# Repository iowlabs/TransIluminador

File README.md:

# TransIluminador

Un transiluminador es un instrumento utilizado en experimentos de biología molecular principalmente en procesos de electroforesis en aplicaciones de PCR, clonación, secuenciación o detección de ADN. Su principio se basa en transmitir luz de longitud e intensidad específica a travez de una muestra, lo cual permite visualizar proteinas específicas o ADN.

Para efectos de la instrumentación, consiste en un dispositivo que controla una gran cantidad de LEDs. De este modo, el dipositivo debe encargarse de generar los voltajes de operación y la corriente de los LEDs. Las variables objetivo para ser controladas son:

- voltaje de operación.
- Intensidad de iluminación.
- Tiempo de exposición.

En algunos dispositivos más complejos existen variables como tipos de curva de iluminación, o algunos cuentan con cámaras para la obtención de imagenes en el dispositivo mismo.
asdavsd

## Requisitos del dispositivo.

El dispositivo a desarrollar debe contar con las siguientes caracteristicas:

1. Alimentación de entrada de 12V. De esto se desprende que el dispositivo debe contar con un regulador DCDC tipo boost para los LEDs.

2. Capacidad de controlar diferentes configuraciónes de LEDs de salida.

3. Control de intensidad de los LEDs por medio de un control lineal de corriente.

4. Driver de corriente de hasta 1A por canal.

4. Capacidad para controlar de forma simultanea 2 canales.

5. Lazo de control para monitoreo y calibración de intensidad luminica.

6. Microcontrolador integrado.

7. Modo de operación manual, stand-alone con curvas pre-configuradas o modo de conexión a un host( pc o web app).

8. Monitoreo de la temperatura de los LEDs y sensor de temperatura externo.

9. Interfaz de usuario por medio de panel y pantalla OLED.

## Revisión del componentes.

Led driver de corriente ajustable

Modulo: LD06AJSA

Amazon: https://www.amazon.com/Adjustable-Current-Driver-30-1500mA-Constant/dp/B07S9C5QF1
Aliexpress: https://es.aliexpress.com/item/32848783838.html?gatewayAdapt=glo2esp

Datasheet no disponible, por observación es un potenciometro y una resistencia de 2.2k aparentemente
Parecido a ejemplos del datasheet de CN5711

Utiliza un CN5711

Datasheet: https://html.alldatasheet.com/html-pdf/1133252/CONSONANCE/CN5711/1403/2/CN5711.html

Otra opción pero más estrecho es NSI50150ADT4G controla entre 150 - 350 mA, 50V Vak max

Datasheet: https://www.onsemi.com/pdf/datasheet/nsi50150ad-d.pdf

Otra opción en rango similar al anterior es MAX16815 35mA - 100 mA
o MAX 16828 35mA - 200 mA
Voltaje de entrada entre 6.5 - 40 V

Datasheet: https://www.analog.com/media/en/technical-documentation/data-sheets/MAX16815-MAX16828.pdf

Existe la posibilidad de hacer una fuente de corriente con 2 PNP y 2 resistencias, la corriente resultante sera producto de ambas resistencias, se puede utilizar una entrada logica o directa para el funcionamiento, se puede reemplazar una ressitencia con un potenciometro y conseguir una fuente variable
Revisar archivo Modulo de corriente.asc

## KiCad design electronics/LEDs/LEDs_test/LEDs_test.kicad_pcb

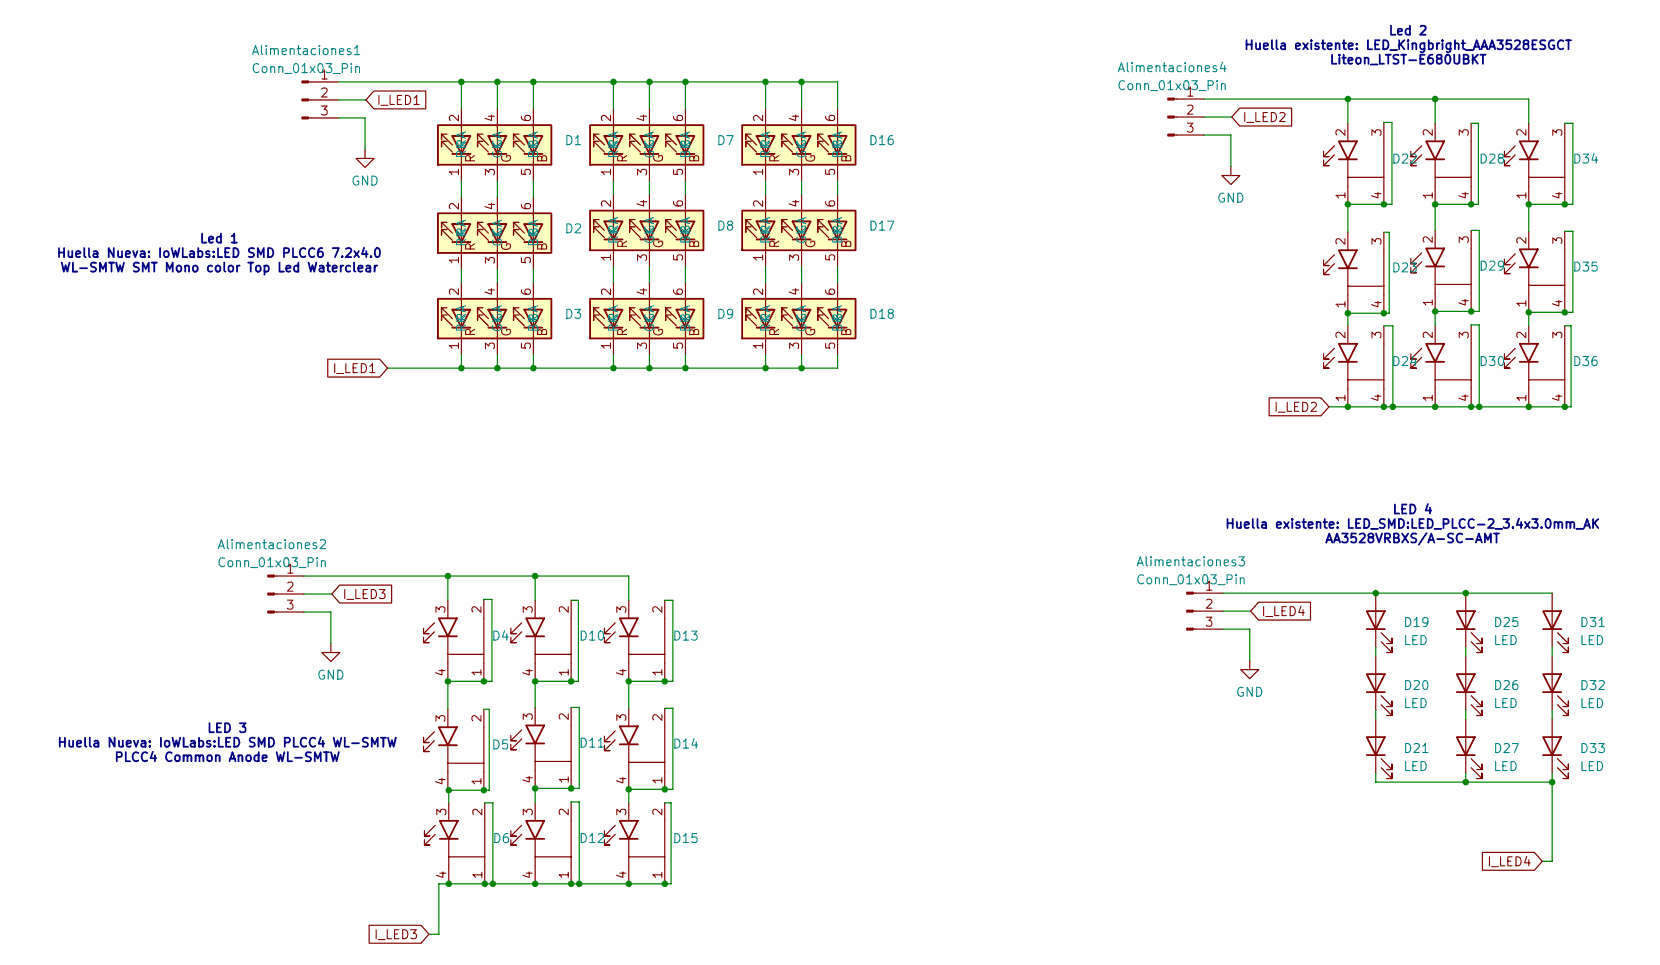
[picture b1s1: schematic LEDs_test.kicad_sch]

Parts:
Alimentaciones1, Alimentaciones2, Alimentaciones3, Alimentaciones4: Conn_01x03_Pin; JST_XH_B3B-XH-A_1x03_P2.50mm_Vertical
D1, D2, D3, D7, D8, D9, D16, D17, D18: LED SMD PLCC6 7.2x4.0
D4, D5, D6, D10, D11, D12, D13, D14, D15: LED SMD PLCC4 WL-SMTW
D19, D20, D21, D25, D26, D27, D31, D32, D33: LED; LED_PLCC-2_3.4x3.0mm_AK
D22, D23, D24, D28, D29, D30, D34, D35, D36: LED_Kingbright_AAA3528ESGCT

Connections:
GND: Alimentaciones1.3, Alimentaciones2.3, Alimentaciones3.3, Alimentaciones4.3
I_LED1: Alimentaciones1.2, D3.1 (RK), D3.3 (GK), D3.5 (BK), D9.1 (RK), D9.3 (GK), D9.5 (BK), D18.1 (RK), D18.3 (GK), D18.5 (BK)
I_LED2: Alimentaciones4.2, D24.1, D24.3, D24.4, D30.1, D30.3, D30.4, D36.1, D36.3, D36.4
I_LED3: Alimentaciones2.2, D6.1, D6.2, D6.4, D12.1, D12.2, D12.4, D15.1, D15.2, D15.4
I_LED4: Alimentaciones3.2, D21.1 (K), D27.1 (K), D33.1 (K)
unnamed: Alimentaciones1.1, D1.2 (RA), D1.4 (GA), D1.6 (BA), D7.2 (RA), D7.4 (GA), D7.6 (BA), D16.2 (RA), D16.4 (GA), D16.6 (BA)
unnamed: Alimentaciones2.1, D4.3, D10.3, D13.3
unnamed: Alimentaciones3.1, D19.2 (A), D25.2 (A), D31.2 (A)
unnamed: Alimentaciones4.1, D22.2, D28.2, D34.2
unnamed: D1.5 (BK), D2.6 (BA)
unnamed: D1.3 (GK), D2.4 (GA)
unnamed: D1.1 (RK), D2.2 (RA)
unnamed: D2.5 (BK), D3.6 (BA)
unnamed: D2.3 (GK), D3.4 (GA)
unnamed: D2.1 (RK), D3.2 (RA)
unnamed: D4.1, D4.2, D4.4, D5.3
unnamed: D5.1, D5.2, D5.4, D6.3
unnamed: D7.5 (BK), D8.6 (BA)
unnamed: D7.3 (GK), D8.4 (GA)
unnamed: D7.1 (RK), D8.2 (RA)
unnamed: D8.5 (BK), D9.6 (BA)
unnamed: D8.3 (GK), D9.4 (GA)
unnamed: D8.1 (RK), D9.2 (RA)
unnamed: D10.1, D10.2, D10.4, D11.3
unnamed: D11.1, D11.2, D11.4, D12.3
unnamed: D13.1, D13.2, D13.4, D14.3
unnamed: D14.1, D14.2, D14.4, D15.3
unnamed: D16.5 (BK), D17.6 (BA)
unnamed: D16.3 (GK), D17.4 (GA)
unnamed: D16.1 (RK), D17.2 (RA)
unnamed: D17.5 (BK), D18.6 (BA)
unnamed: D17.3 (GK), D18.4 (GA)
unnamed: D17.1 (RK), D18.2 (RA)
unnamed: D19.1 (K), D20.2 (A)
unnamed: D20.1 (K), D21.2 (A)
unnamed: D22.1, D22.3, D22.4, D23.2
unnamed: D23.1, D23.3, D23.4, D24.2
unnamed: D25.1 (K), D26.2 (A)
unnamed: D26.1 (K), D27.2 (A)
unnamed: D28.1, D28.3, D28.4, D29.2
unnamed: D29.1, D29.3, D29.4, D30.2
unnamed: D31.1 (K), D32.2 (A)
unnamed: D32.1 (K), D33.2 (A)
unnamed: D34.1, D34.3, D34.4, D35.2
unnamed: D35.1, D35.3, D35.4, D36.2

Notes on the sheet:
LED 4 Huella existente: LED_SMD:LED_PLCC-2_3.4x3.0mm_AK AA3528VRBXS/A-SC-AMT
Led 1 Huella Nueva: IoWLabs:LED SMD PLCC6 7.2x4.0 WL-SMTW SMT Mono color Top Led Waterclear
Led 2 Huella existente: LED_Kingbright_AAA3528ESGCT Liteon_LTST-E680UBKT
LED 3 Huella Nueva: IoWLabs:LED SMD PLCC4 WL-SMTW PLCC4 Common Anode WL-SMTW

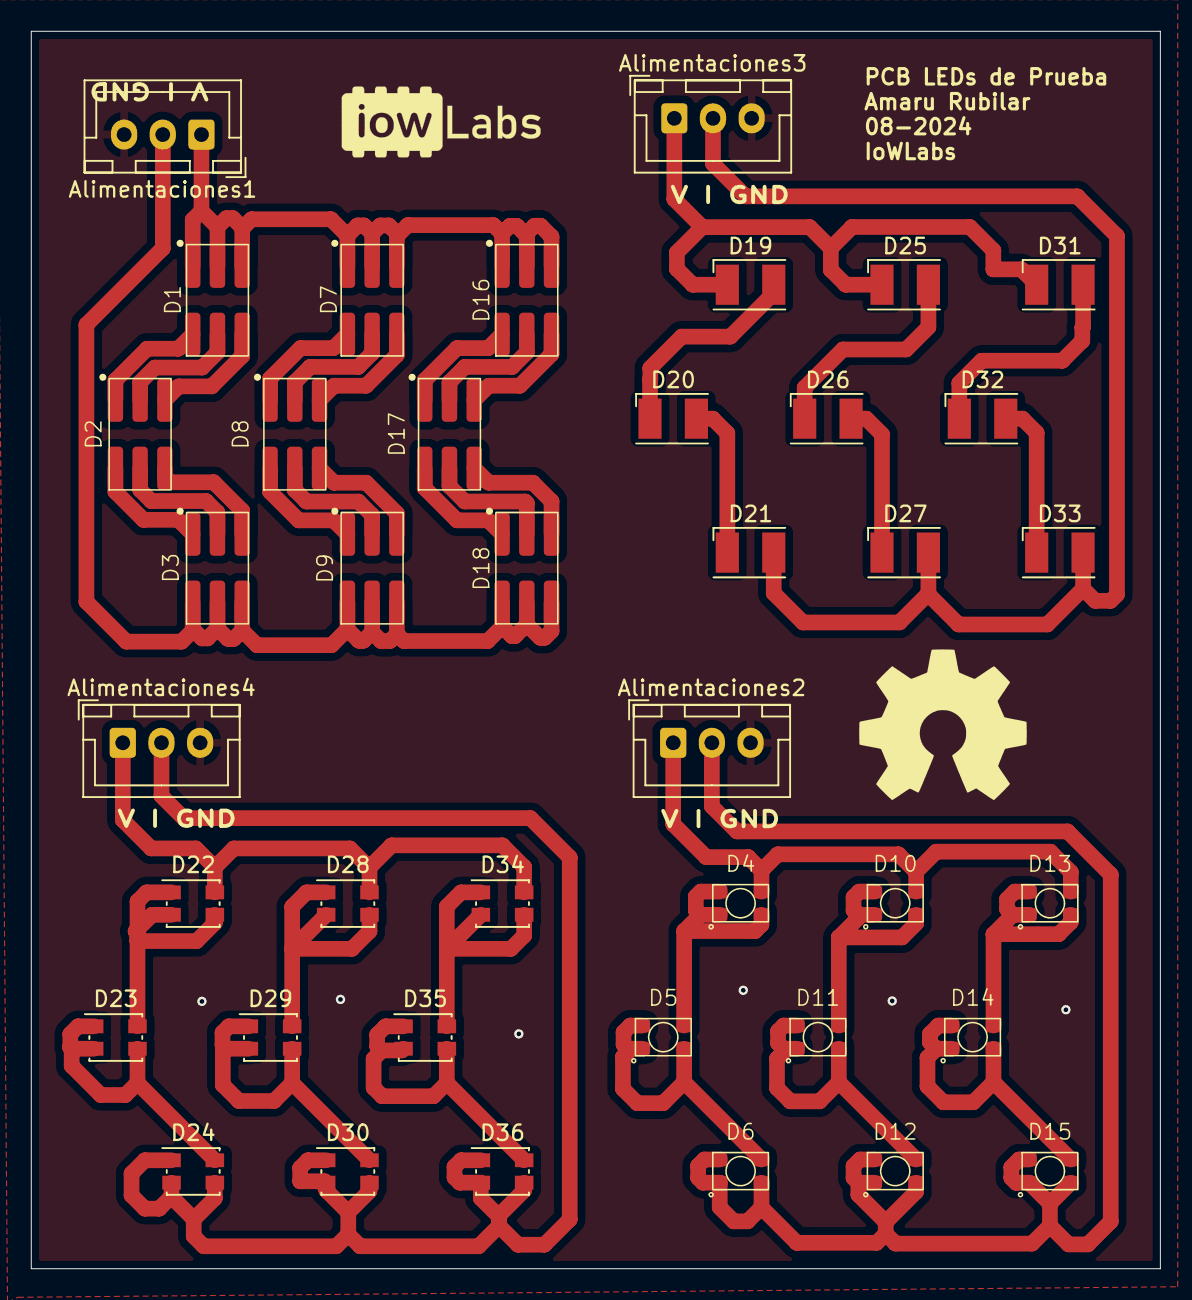
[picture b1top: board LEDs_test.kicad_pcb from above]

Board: 2 copper layers, 73.0 x 80.0 mm, 40 parts (0 on the bottom side), 45 nets.

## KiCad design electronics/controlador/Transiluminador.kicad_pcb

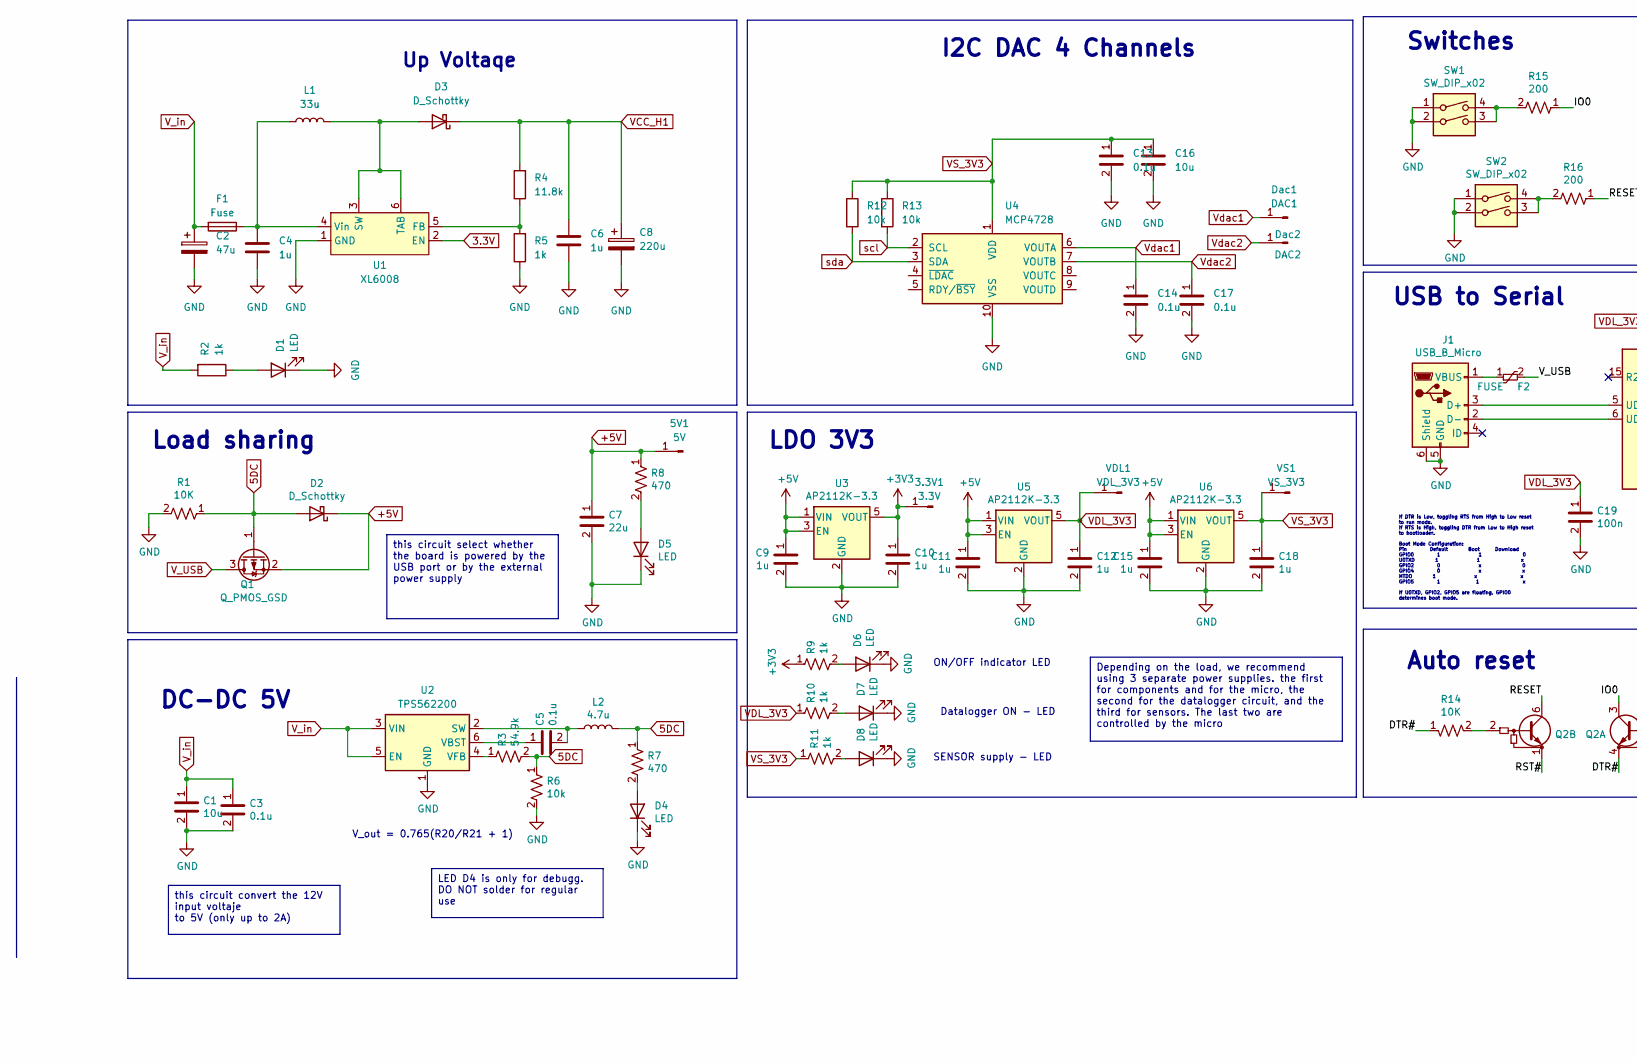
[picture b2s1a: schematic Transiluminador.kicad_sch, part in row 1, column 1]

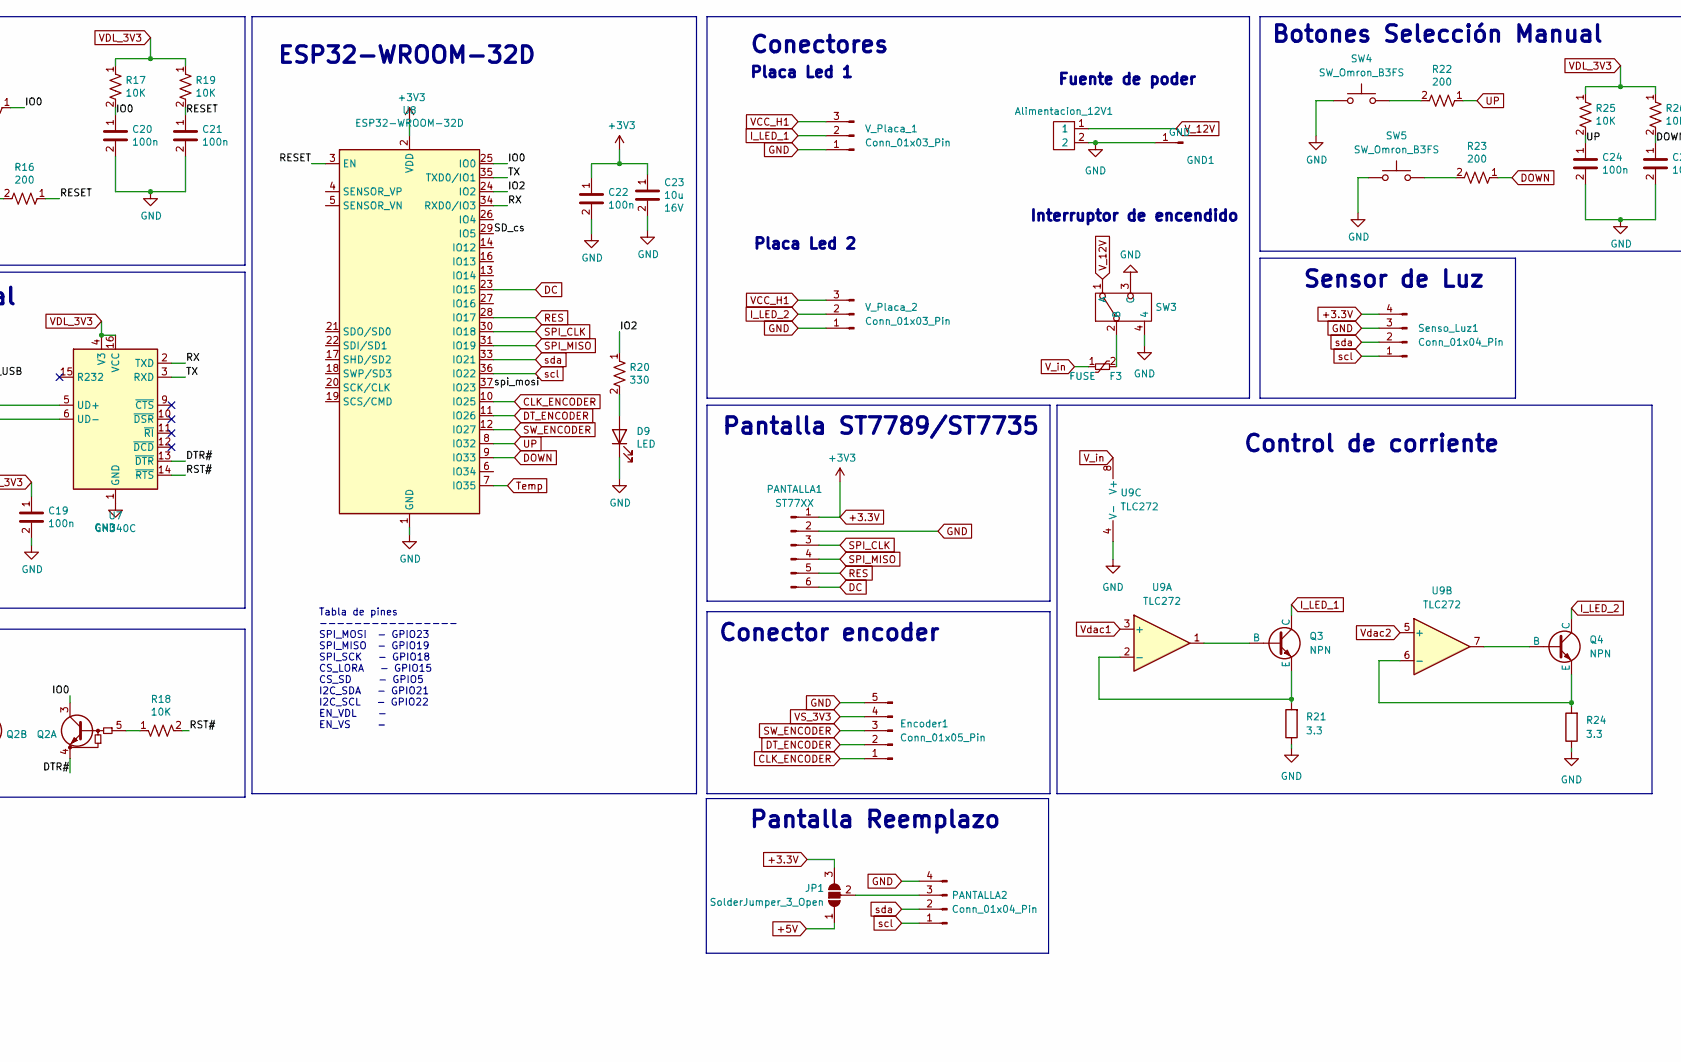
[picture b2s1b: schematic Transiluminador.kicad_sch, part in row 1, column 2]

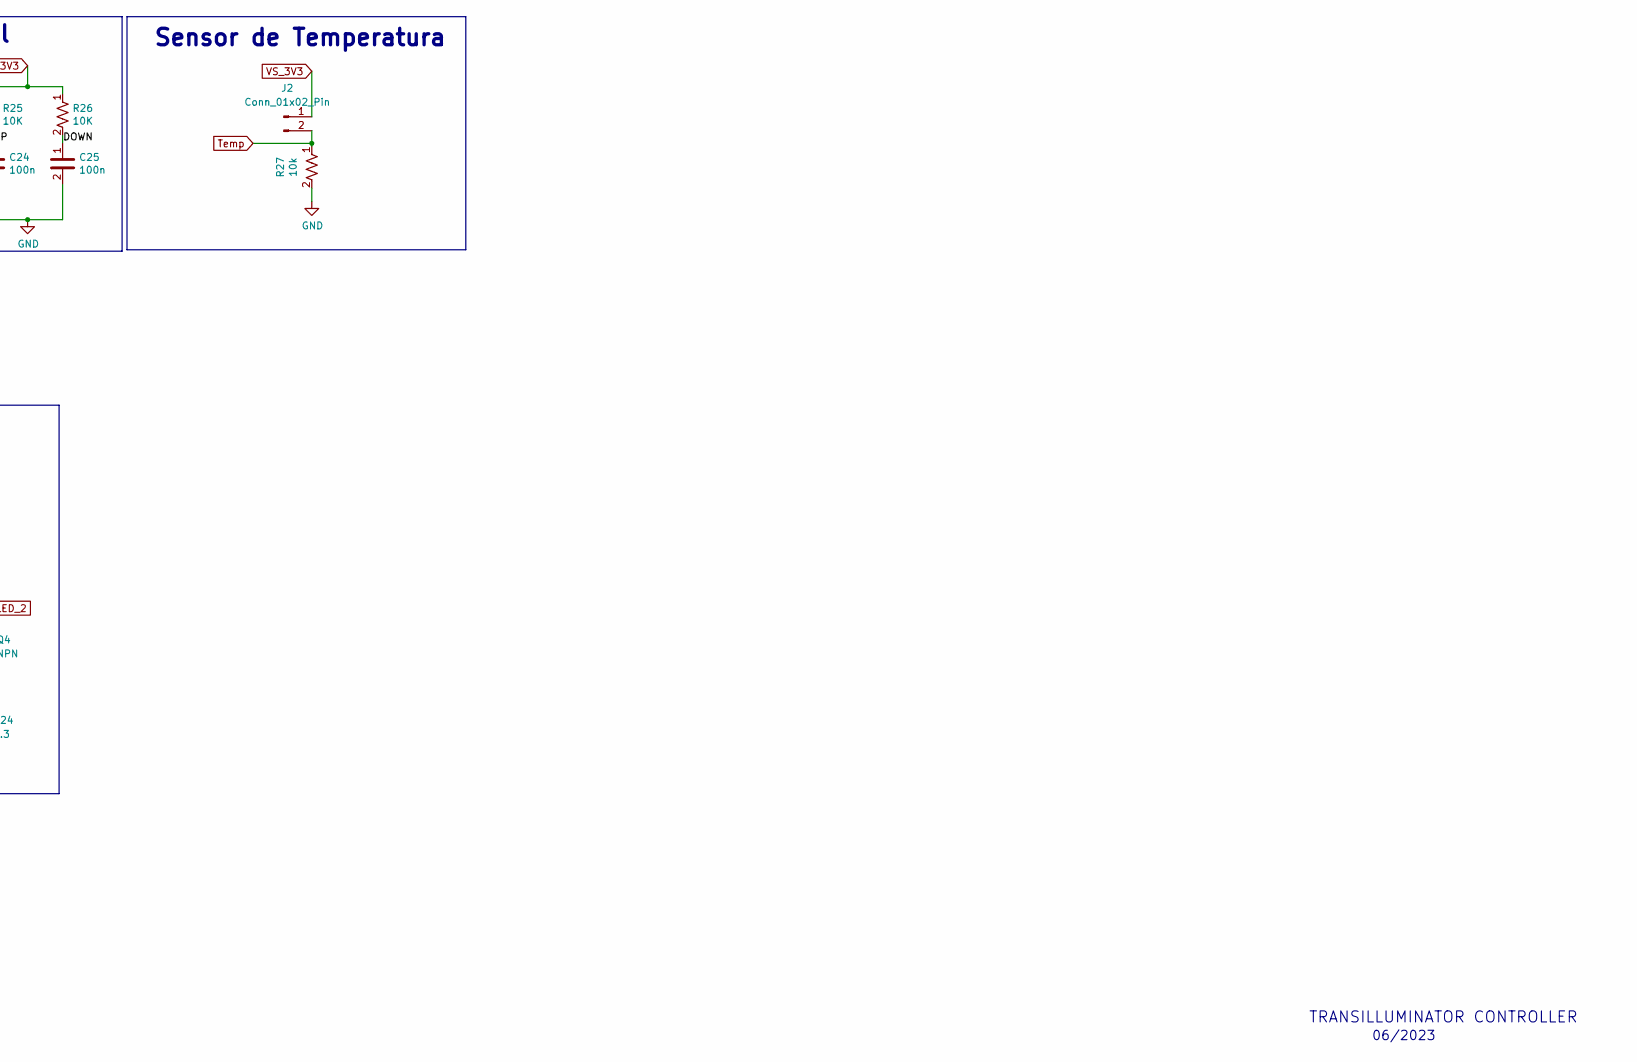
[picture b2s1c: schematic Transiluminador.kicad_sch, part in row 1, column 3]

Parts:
3.3V1: 3.3V; TestPoint_Loop_D2.50mm_Drill1.0mm_LowProfile
5V1: 5V; TestPoint_Loop_D2.50mm_Drill1.0mm_LowProfile
Alimentacion_12V1: HDR-2x1; JST_XH_B2B-XH-A_1x02_P2.50mm_Vertical
C1, C23: 10u; C_0805_2012Metric; Voltage rated 16V
C2: 47u; CP_Elec_6.3x7.7
C3, C5: 0.1u; C_0805_2012Metric; Voltage rated 16V
C4, C6: 1u; C_0805_2012Metric
C7: 22u; C_0805_2012Metric; Voltage rated 16V
C8: 220u; CP_Elec_10x10.5
C9, C10, C11, C12, C15, C18: 1u; C_0603_1608Metric; Voltage rated 16V
C13, C14, C17: 0.1u; C_0603_1608Metric; Voltage rated 16V
C16: 10u; C_0603_1608Metric; Voltage rated 16V
C19, C20, C21, C22, C24, C25: 100n; C_0603_1608Metric; Voltage rated 16V
D1, D4, D5, D6, D7, D8, D9: LED; LED_0603_1608Metric
D2, D3: D_Schottky; D_SMA
Dac1: DAC1; TestPoint_Loop_D2.50mm_Drill1.0mm_LowProfile
Dac2: DAC2; TestPoint_Loop_D2.50mm_Drill1.0mm_LowProfile
Encoder1: Conn_01x05_Pin; JST_XH_B5B-XH-A_1x05_P2.50mm_Vertical
F1: Fuse; Fuse_1206_3216Metric
F2, F3: FUSE; Fuse_1206_3216Metric
GND1: GND; TestPoint_Loop_D2.50mm_Drill1.0mm_LowProfile
J1: USB_B_Micro; USB_Micro-B_Amphenol_10118194_Horizontal
J2: Conn_01x02_Pin; JST_XH_B2B-XH-A_1x02_P2.50mm_Vertical
JP1: SolderJumper_3_Open; SolderJumper-3_P1.3mm_Open_RoundedPad1.0x1.5mm
L1: 33u; L_12x12mm_H8mm
L2: 4.7u; L_Bourns_SRP7028A_7.3x6.6mm
PANTALLA1: ST77XX; JST_XH_B6B-XH-A_1x06_P2.50mm_Vertical
PANTALLA2: Conn_01x04_Pin; JST_XH_B4B-XH-A_1x04_P2.50mm_Vertical
Q1: Q_PMOS_GSD; SOT-23
Q2: Q_Dual_NPN_NPN_BRT_E1B1C2E2B2C1; SOT-363_SC-70-6_Handsoldering
Q3, Q4: NPN; SOT-223-3_TabPin2
R1, R14, R17, R18, R19, R25, R26: 10K; R_0603_1608Metric
R2, R5, R9, R10, R11: 1k; R_0603_1608Metric
R3: 54.9k; R_0603_1608Metric
R4: 11.8k; R_0603_1608Metric
R6, R12, R13, R27: 10k; R_0603_1608Metric
R7, R8: 470; R_0603_1608Metric
R15, R16, R22, R23: 200; R_0603_1608Metric
R20: 330; R_0603_1608Metric
R21, R24: 3.3; TO-263-3 TAB 3
SW1, SW2: SW_DIP_x02; SMD_SWITCH
SW3: SS-SK12D07VG4-SDDT
SW4, SW5: SW_Omron_B3FS; JST_XH_B2B-XH-A_1x02_P2.50mm_Vertical
Senso_Luz1: Conn_01x04_Pin; JST_XH_B4B-XH-A_1x04_P2.50mm_Vertical
U1: XL6008; TO-252-5_TabPin6
U2: TPS562200; SOT-23-6
U3, U5, U6: AP2112K-3.3; SOT-23-5
U4: MCP4728; MSOP-10_3x3mm_P0.5mm
U7: CH340C; SOIC-16_3.9x9.9mm_P1.27mm
U8: ESP32-WROOM-32D; ESP32-WROOM-32
U9: TLC272; SOIC-8_3.9x4.9mm_P1.27mm
VDL1: VDL_3V3; TestPoint_Loop_D2.50mm_Drill1.0mm_LowProfile
VS1: VS_3V3; TestPoint_Loop_D2.50mm_Drill1.0mm_LowProfile
V_Placa_1, V_Placa_2: Conn_01x03_Pin; JST_XH_B3B-XH-A_1x03_P2.50mm_Vertical

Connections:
3.3V: U1.2 (EN)
5DC: D2.2 (A), L2.2, Q1.1 (G), R1.1, R3.2, R6.1, R7.1
+3.3V: 3.3V1.1, C10.1, C22.1, C23.1, JP1.3 (B), PANTALLA1.1, R9.1, Senso_Luz1.4, U3.5 (VOUT), U8.2 (VDD)
+5V: 5V1.1, C7.1, C9.1, C11.1, C15.1, D2.1 (K), JP1.1 (A), Q1.2 (S), R8.1, U3.1 (VIN), U3.3 (EN), U5.1 (VIN), U5.3 (EN), U6.1 (VIN), U6.3 (EN)
/DTR#: Q2.4 (E1), R14.1, U7.13 (~DTR)
/IO0: C20.1, Q2.3 (C1), R15.1, R17.2, U8.25 (IO0)
/IO2: R20.1, U8.24 (IO2)
/RESET: C21.1, Q2.6 (C1), R16.1, R19.2, U8.3 (EN)
/RST#: Q2.1 (E1), R18.2, U7.14 (~RTS)
/RX: U7.2 (TXD), U8.34 (RXD0/IO3)
/SD_cs: U8.29 (IO5)
/TX: U7.3 (RXD), U8.35 (TXD0/IO1)
/spi_mosi: U8.37 (IO23)
CLK_ENCODER: Encoder1.1, U8.10 (IO25)
DC: PANTALLA1.6, U8.23 (IO15)
DOWN: C25.1, R23.1, R26.2, U8.9 (IO33)
DT_ENCODER: Encoder1.2, U8.11 (IO26)
GND: Alimentacion_12V1.2, C1.2, C2.2, C3.2, C4.2, C6.2, C7.2, C8.2, C9.2, C10.2, C11.2, C12.2, C13.2, C14.2, C15.2, C16.2, C17.2, C18.2, C19.2, C20.2, C21.2, C22.2, C23.2, C24.2, C25.2, D1.1 (K), D4.1 (K), D5.1 (K), D6.1 (K), D7.1 (K), D8.1 (K), D9.1 (K), Encoder1.5, GND1.1, J1.5 (GND), J1.6 (Shield), PANTALLA1.2, PANTALLA2.4, R1.2, R5.1, R6.2, R21.1, R24.1, R27.2, SW1.1, SW1.2, SW2.1, SW2.2, SW3.3 (C), SW3.4, SW4.1, SW5.1, Senso_Luz1.3, U1.1 (GND), U2.1 (GND), U3.2 (GND), U4.10 (VSS), U5.2 (GND), U6.2 (GND), U7.1 (GND), U8.1 (GND), U8.15 (GND), U8.38 (GND), U8.39 (GND), U9.4 (V-), V_Placa_1.1, V_Placa_2.1
I_LED_1: Q3.1 (C), V_Placa_1.2
I_LED_2: Q4.1 (C), V_Placa_2.2
unnamed: D1.2 (A), R2.1
unnamed: D3.2 (A), L1.2, U1.3 (SW), U1.6 (TAB)
unnamed: D4.2 (A), R7.2
unnamed: D5.2 (A), R8.2
unnamed: D6.2 (A), R9.2
unnamed: D7.2 (A), R10.2
unnamed: D8.2 (A), R11.2
unnamed: D9.2 (A), R20.2
unnamed: J1.3 (D+), U7.5 (UD+)
unnamed: J1.2 (D-), U7.6 (UD-)
unnamed: F2.1, J1.1 (VBUS)
unnamed: JP1.2 (C), PANTALLA2.3
unnamed: Q2.5 (B1), R18.1
unnamed: Q2.2 (B1), R14.2
unnamed: Q3.2 (B), U9.1
unnamed: Q3.3 (E), R21.2, U9.2 (-)
unnamed: Q4.2 (B), U9.7
unnamed: Q4.3 (E), R24.2, U9.6 (-)
unnamed: R15.2, SW1.3, SW1.4
unnamed: R16.2, SW2.3, SW2.4
unnamed: R22.2, SW4.2
unnamed: R23.2, SW5.2
unnamed: F3.2, SW3.2 (B)
unnamed: R4.1, R5.2, U1.5 (FB)
unnamed: C4.1, F1.1, L1.1, U1.4 (Vin)
unnamed: C5.2, L2.1, U2.2 (SW)
unnamed: C5.1, U2.6 (VBST)
unnamed: R3.1, U2.4 (VFB)
RES: PANTALLA1.5, U8.28 (IO17)
SPI_CLK: PANTALLA1.3, U8.30 (IO18)
SPI_MISO: PANTALLA1.4, U8.31 (IO19)
SW_ENCODER: Encoder1.3, U8.12 (IO27)
Temp: J2.2, R27.1, U8.7 (IO35)
UP: C24.1, R22.1, R25.2, U8.8 (IO32)
VCC_H1: C6.1, C8.1, D3.1 (K), R4.2, V_Placa_1.3, V_Placa_2.3
VDL_3V3: C12.1, C19.1, R10.1, R17.1, R19.1, R25.1, R26.1, U5.5 (VOUT), U7.4 (V3), U7.16 (VCC), VDL1.1
VS_3V3: C13.1, C16.1, C18.1, Encoder1.4, J2.1, R11.1, R12.1, R13.1, U4.1 (VDD), U6.5 (VOUT), VS1.1
V_12V: Alimentacion_12V1.1, SW3.1 (A)
V_USB: F2.2, Q1.3 (D)
V_in: C1.1, C2.1, C3.1, F1.2, F3.1, R2.2, U2.3 (VIN), U2.5 (EN), U9.8 (V+)
Vdac1: C14.1, Dac1.1, U4.6 (VOUTA), U9.3 (+)
Vdac2: C17.1, Dac2.1, U4.7 (VOUTB), U9.5 (+)
scl: PANTALLA2.1, R13.2, Senso_Luz1.1, U4.2 (SCL), U8.36 (IO22)
sda: PANTALLA2.2, R12.2, Senso_Luz1.2, U4.3 (SDA), U8.33 (IO21)

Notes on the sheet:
LED D4 is only for debugg. DO NOT solder for regular use
Depending on the load, we recommend using 3 separate power supplies. the first for components and for the micro, the second for the datalogger circuit, and the third for sensors. The last two are controlled by the micro
this circuit select whether the board is powered by the USB port or by the external power supply
this circuit convert the 12V input voltaje to 5V (only up to 2A)
USB to Serial
Pantalla Reemplazo
I2C DAC 4 Channels
Placa Led 1
Placa Led 2
Tabla de pines ---------------- SPI_MOSI - GPIO23 SPI_MISO - GPIO19 SPI_SCK - GPIO18 CS_LORA - GPIO15 CS_SD - GPIO5 I2C_SDA - GPIO21 I2C_SCL - GPIO22 EN_VDL - EN_VS -
SENSOR supply - LED
Pantalla ST7789/ST7735
Conectores
Interruptor de encendido
Fuente de poder
06/2023
Up Voltaqe
DC-DC 5V
Switches
Auto reset
ESP32-WROOM-32D
If DTR is Low, toggling RTS from High to Low reset to run mode. If RTS is High, toggling DTR from Low to High reset to bootloader. Boot Mode Configuration: Pin Default Boot Download GPIO0 1 1 0 U0TXD 1 1 x GPIO2 0 x 0 GPIO4 0 x x MTDO 1 x x GPIO5 1 1 x If U0TXD, GPIO2, GPIO5 are floating, GPIO0 det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
V_out = 0.765(R20/R21 + 1)
ON/OFF indicator LED
Control de corriente
LDO 3V3
Botones Selección Manual
Load sharing
Conector encoder
Sensor de Luz
TRANSILLUMINATOR CONTROLLER
Sensor de Temperatura
Datalogger ON - LED

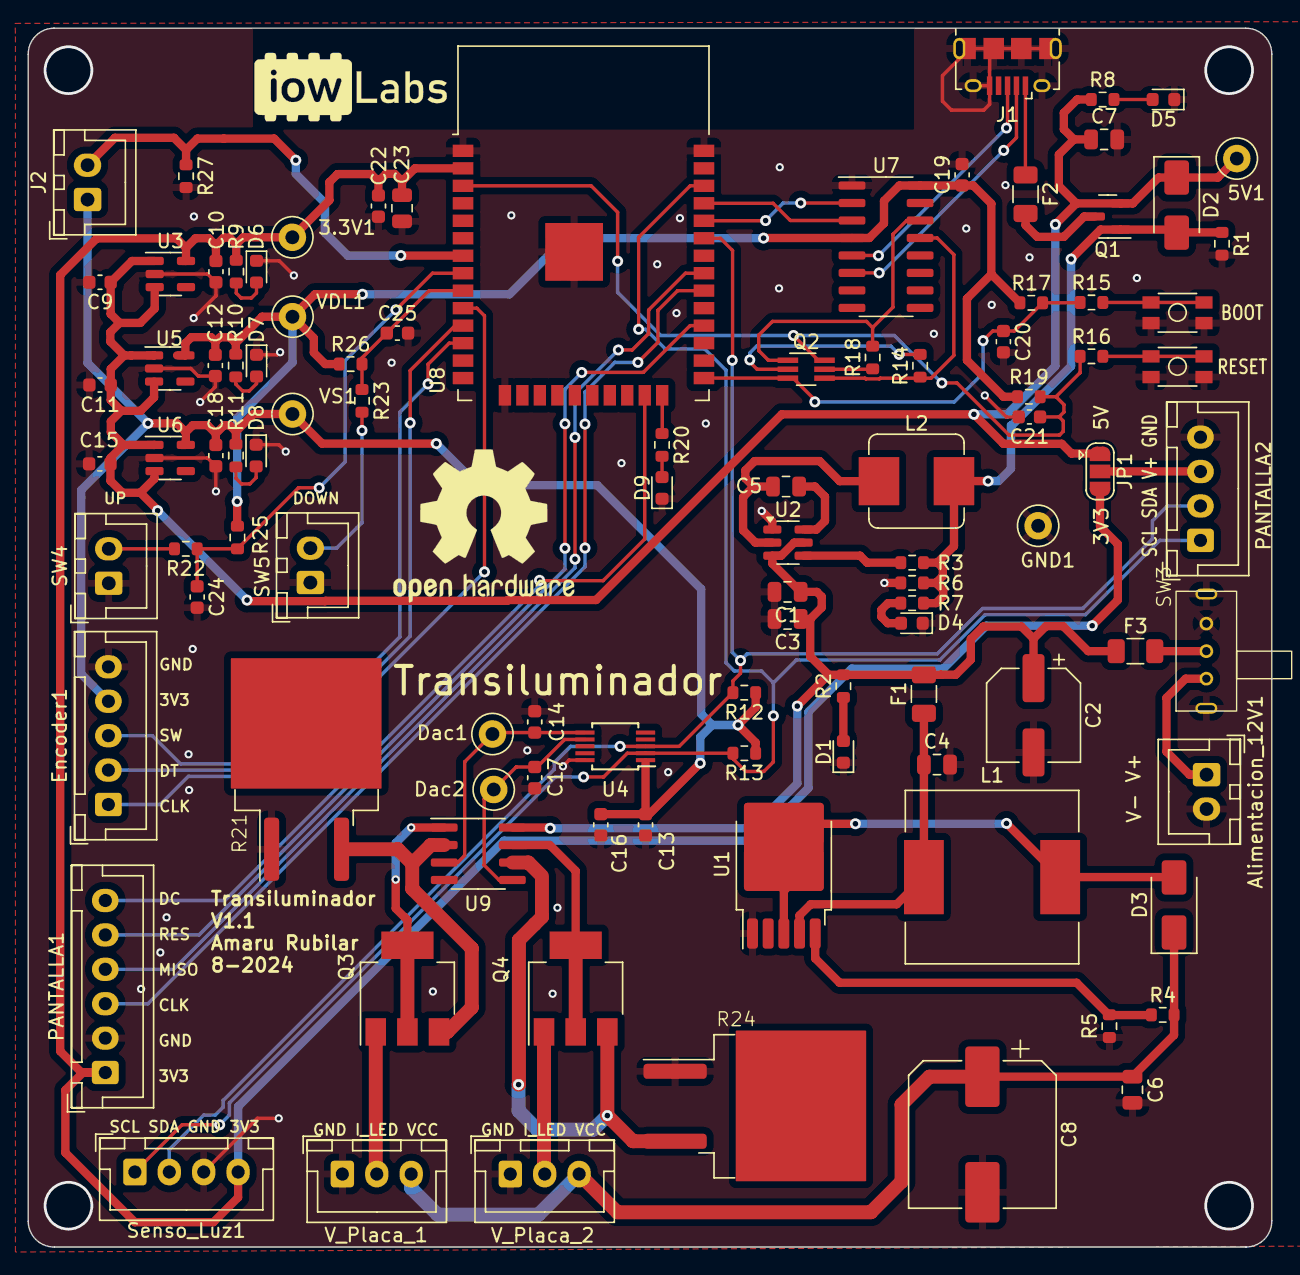
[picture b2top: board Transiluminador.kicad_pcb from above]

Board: 2 copper layers, 90.3 x 88.5 mm, 101 parts (0 on the bottom side), 61 nets.

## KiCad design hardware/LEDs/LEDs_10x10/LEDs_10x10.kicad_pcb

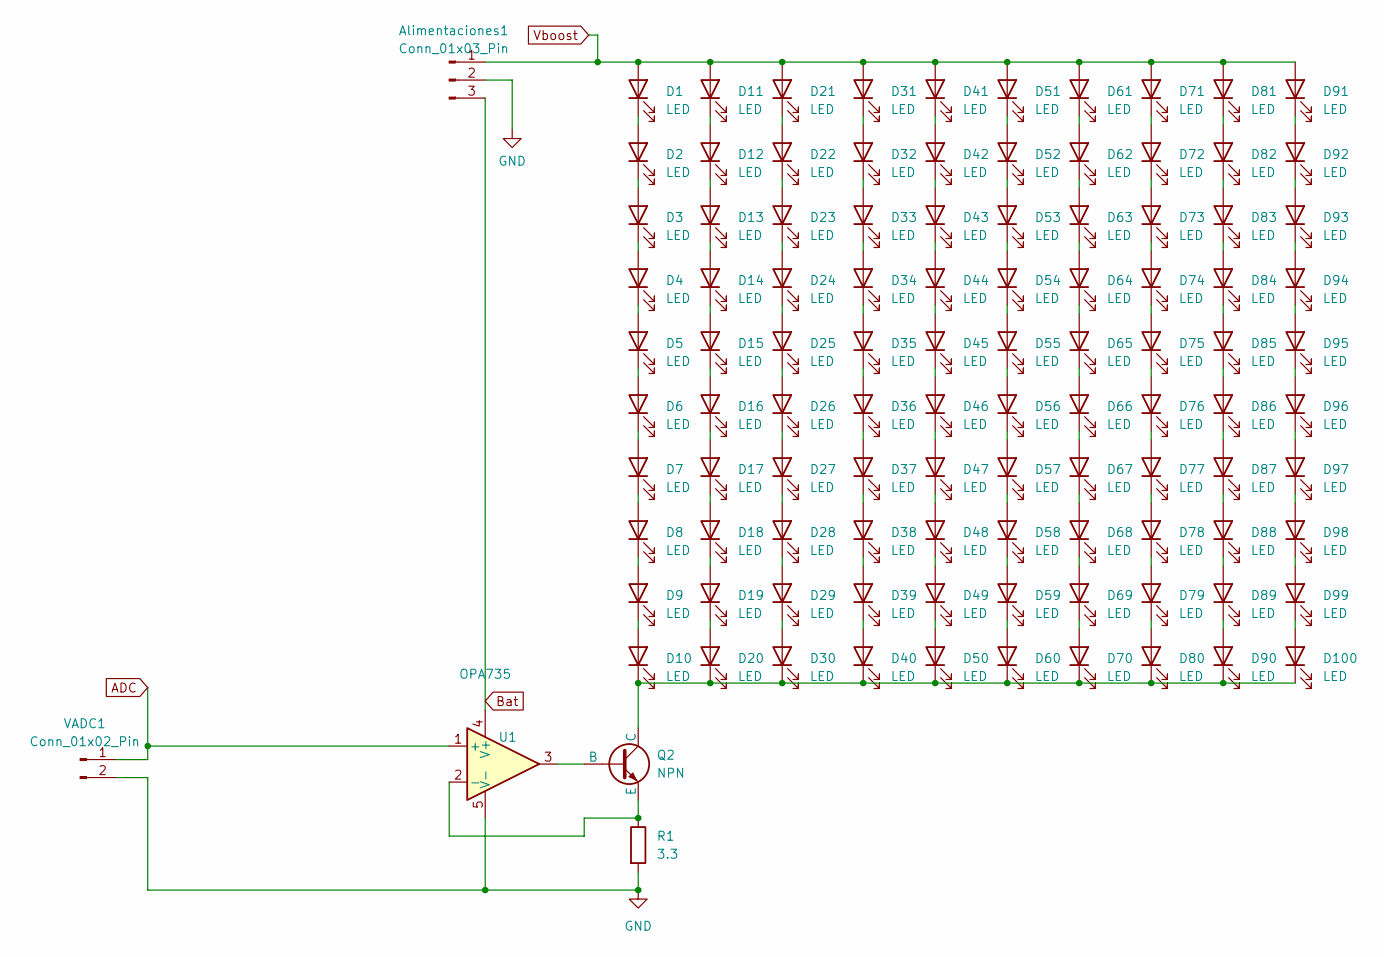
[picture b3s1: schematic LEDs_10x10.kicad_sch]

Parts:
Alimentaciones1: Conn_01x03_Pin; JST_XH_B3B-XH-A_1x03_P2.50mm_Vertical
D1, D2, D3, D4, D5, D6, D7, D8, D9, D10, D11, D12, D13, D14, D15, D16, D17, D18, D19, D20, D21, D22, D23, D24, D25, D26, D27, D28, D29, D30, D31, D32, D33, D34, D35, D36, D37, D38, D39, D40, D41, D42, D43, D44, D45, D46, D47, D48, D49, D50, D51, D52, D53, D54, D55, D56, D57, D58, D59, D60, D61, D62, D63, D64, D65, D66, D67, D68, D69, D70, D71, D72, D73, D74, D75, D76, D77, D78, D79, D80, D81, D82, D83, D84, D85, D86, D87, D88, D89, D90, D91, D92, D93, D94, D95, D96, D97, D98, D99, D100: LED; LED_Rectangular_W5.0mm_H2.0mm_Horizontal_O3.81mm_Z3.0mm
Q2: NPN; SOT-223
R1: 3.3; R_0603_1608Metric
U1: OPA735; TSOT-23-5_HandSoldering
VADC1: Conn_01x02_Pin; JST_XH_B2B-XH-A_1x02_P2.50mm_Vertical

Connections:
ADC: U1.1 (+), VADC1.1
Bat: Alimentaciones1.3, U1.4 (V+)
GND: Alimentaciones1.2, R1.2, U1.5 (V-), VADC1.2
unnamed: D1.1 (K), D2.2 (A)
unnamed: D2.1 (K), D3.2 (A)
unnamed: D3.1 (K), D4.2 (A)
unnamed: D4.1 (K), D5.2 (A)
unnamed: D5.1 (K), D6.2 (A)
unnamed: D6.1 (K), D7.2 (A)
unnamed: D7.1 (K), D8.2 (A)
unnamed: D8.1 (K), D9.2 (A)
unnamed: D9.1 (K), D10.2 (A)
unnamed 12: D10.1 (K), D20.1 (K), D30.1 (K), D40.1 (K), D50.1 (K), D60.1 (K), D70.1 (K), D80.1 (K), D90.1 (K), D100.1 (K); also elsewhere on the board
unnamed: D11.1 (K), D12.2 (A)
unnamed: D12.1 (K), D13.2 (A)
unnamed: D13.1 (K), D14.2 (A)
unnamed: D14.1 (K), D15.2 (A)
unnamed: D15.1 (K), D16.2 (A)
unnamed: D16.1 (K), D17.2 (A)
unnamed: D17.1 (K), D18.2 (A)
unnamed: D18.1 (K), D19.2 (A)
unnamed: D19.1 (K), D20.2 (A)
unnamed: D21.1 (K), D22.2 (A)
unnamed: D22.1 (K), D23.2 (A)
unnamed: D23.1 (K), D24.2 (A)
unnamed: D24.1 (K), D25.2 (A)
unnamed: D25.1 (K), D26.2 (A)
unnamed: D26.1 (K), D27.2 (A)
unnamed: D27.1 (K), D28.2 (A)
unnamed: D28.1 (K), D29.2 (A)
unnamed: D29.1 (K), D30.2 (A)
unnamed: D31.1 (K), D32.2 (A)
unnamed: D32.1 (K), D33.2 (A)
unnamed: D33.1 (K), D34.2 (A)
unnamed: D34.1 (K), D35.2 (A)
unnamed: D35.1 (K), D36.2 (A)
unnamed: D36.1 (K), D37.2 (A)
unnamed: D37.1 (K), D38.2 (A)
unnamed: D38.1 (K), D39.2 (A)
unnamed: D39.1 (K), D40.2 (A)
unnamed: D41.1 (K), D42.2 (A)
unnamed: D42.1 (K), D43.2 (A)
unnamed: D43.1 (K), D44.2 (A)
unnamed: D44.1 (K), D45.2 (A)
unnamed: D45.1 (K), D46.2 (A)
unnamed: D46.1 (K), D47.2 (A)
unnamed: D47.1 (K), D48.2 (A)
unnamed: D48.1 (K), D49.2 (A)
unnamed: D49.1 (K), D50.2 (A)
unnamed: D51.1 (K), D52.2 (A)
unnamed: D52.1 (K), D53.2 (A)
unnamed: D53.1 (K), D54.2 (A)
unnamed: D54.1 (K), D55.2 (A)
unnamed: D55.1 (K), D56.2 (A)
unnamed: D56.1 (K), D57.2 (A)
unnamed: D57.1 (K), D58.2 (A)
unnamed: D58.1 (K), D59.2 (A)
unnamed: D59.1 (K), D60.2 (A)
unnamed: D61.1 (K), D62.2 (A)
unnamed: D62.1 (K), D63.2 (A)
unnamed: D63.1 (K), D64.2 (A)
unnamed: D64.1 (K), D65.2 (A)
unnamed: D65.1 (K), D66.2 (A)
unnamed: D66.1 (K), D67.2 (A)
unnamed: D67.1 (K), D68.2 (A)
unnamed: D68.1 (K), D69.2 (A)
unnamed: D69.1 (K), D70.2 (A)
unnamed: D71.1 (K), D72.2 (A)
unnamed: D72.1 (K), D73.2 (A)
unnamed: D73.1 (K), D74.2 (A)
unnamed: D74.1 (K), D75.2 (A)
unnamed: D75.1 (K), D76.2 (A)
unnamed: D76.1 (K), D77.2 (A)
unnamed: D77.1 (K), D78.2 (A)
unnamed: D78.1 (K), D79.2 (A)
unnamed: D79.1 (K), D80.2 (A)
unnamed: D81.1 (K), D82.2 (A)
unnamed: D82.1 (K), D83.2 (A)
unnamed: D83.1 (K), D84.2 (A)
unnamed: D84.1 (K), D85.2 (A)
unnamed: D85.1 (K), D86.2 (A)
unnamed: D86.1 (K), D87.2 (A)
unnamed: D87.1 (K), D88.2 (A)
unnamed: D88.1 (K), D89.2 (A)
unnamed: D89.1 (K), D90.2 (A)
unnamed: D91.1 (K), D92.2 (A)
unnamed: D92.1 (K), D93.2 (A)
unnamed: D93.1 (K), D94.2 (A)
unnamed: D94.1 (K), D95.2 (A)
unnamed: D95.1 (K), D96.2 (A)
unnamed: D96.1 (K), D97.2 (A)
unnamed: D97.1 (K), D98.2 (A)
unnamed: D98.1 (K), D99.2 (A)
unnamed: D99.1 (K), D100.2 (A)
unnamed 94: U1.3; also elsewhere on the board
unnamed 95: R1.1, U1.2 (-); also elsewhere on the board
Vboost: Alimentaciones1.1, D1.2 (A), D11.2 (A), D21.2 (A), D31.2 (A), D41.2 (A), D51.2 (A), D61.2 (A), D71.2 (A), D81.2 (A), D91.2 (A)

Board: 2 copper layers, 105 parts (0 on the bottom side), 97 nets, no tracks yet.

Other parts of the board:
Q1: NPN; SOT-223

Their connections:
unnamed 12: Q1.1 (C); also elsewhere on the board
unnamed 94: Q1.2 (B); also elsewhere on the board
unnamed 95: Q1.3 (E); also elsewhere on the board

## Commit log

2023-12-15 adding requirements
2023-12-15 update readme v2
2023-12-18 adding blue LEDS datasheet
2023-12-18 actualización
2023-12-21 pcb_lista
2023-12-21 editchico
2023-12-26 sensorluz
2024-01-12 simulación
2024-01-17 v1.1
2024-01-18 esquinas
2024-01-18 minimos
2024-01-26 cambios_pcb
2024-07-26 actualizacion_loadsharing
2024-08-19 changing name for folder hardware
2024-08-20 Arreglo_5V_Pantalla
2024-08-20 sensor_temp
2024-08-20 Esquematico_LEDS_Test
2024-08-20 PCB_LEDs_Test
2024-08-20 Letras_PCB
